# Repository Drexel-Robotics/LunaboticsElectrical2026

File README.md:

# Lunabotics Electrical 2025/2026 🚀⚡

Electrical and Embedded Systems repository for the Lunabotics 2025/2026 competition.

This repository contains firmware, hardware design files, and supporting documentation for the Lunabotics robot electrical subsystem — including embedded control (STM32 + Arduino), actuator drivers, power systems, and safety systems.

---

## 📌 Overview

The LunaboticsElectrical2026 project focuses on:

- Embedded motor & actuator control
- Custom PCB design (KiCAD)

This repo will grow throughout the season as firmware and hardware designs mature.

---

## 📂 Repository Structure

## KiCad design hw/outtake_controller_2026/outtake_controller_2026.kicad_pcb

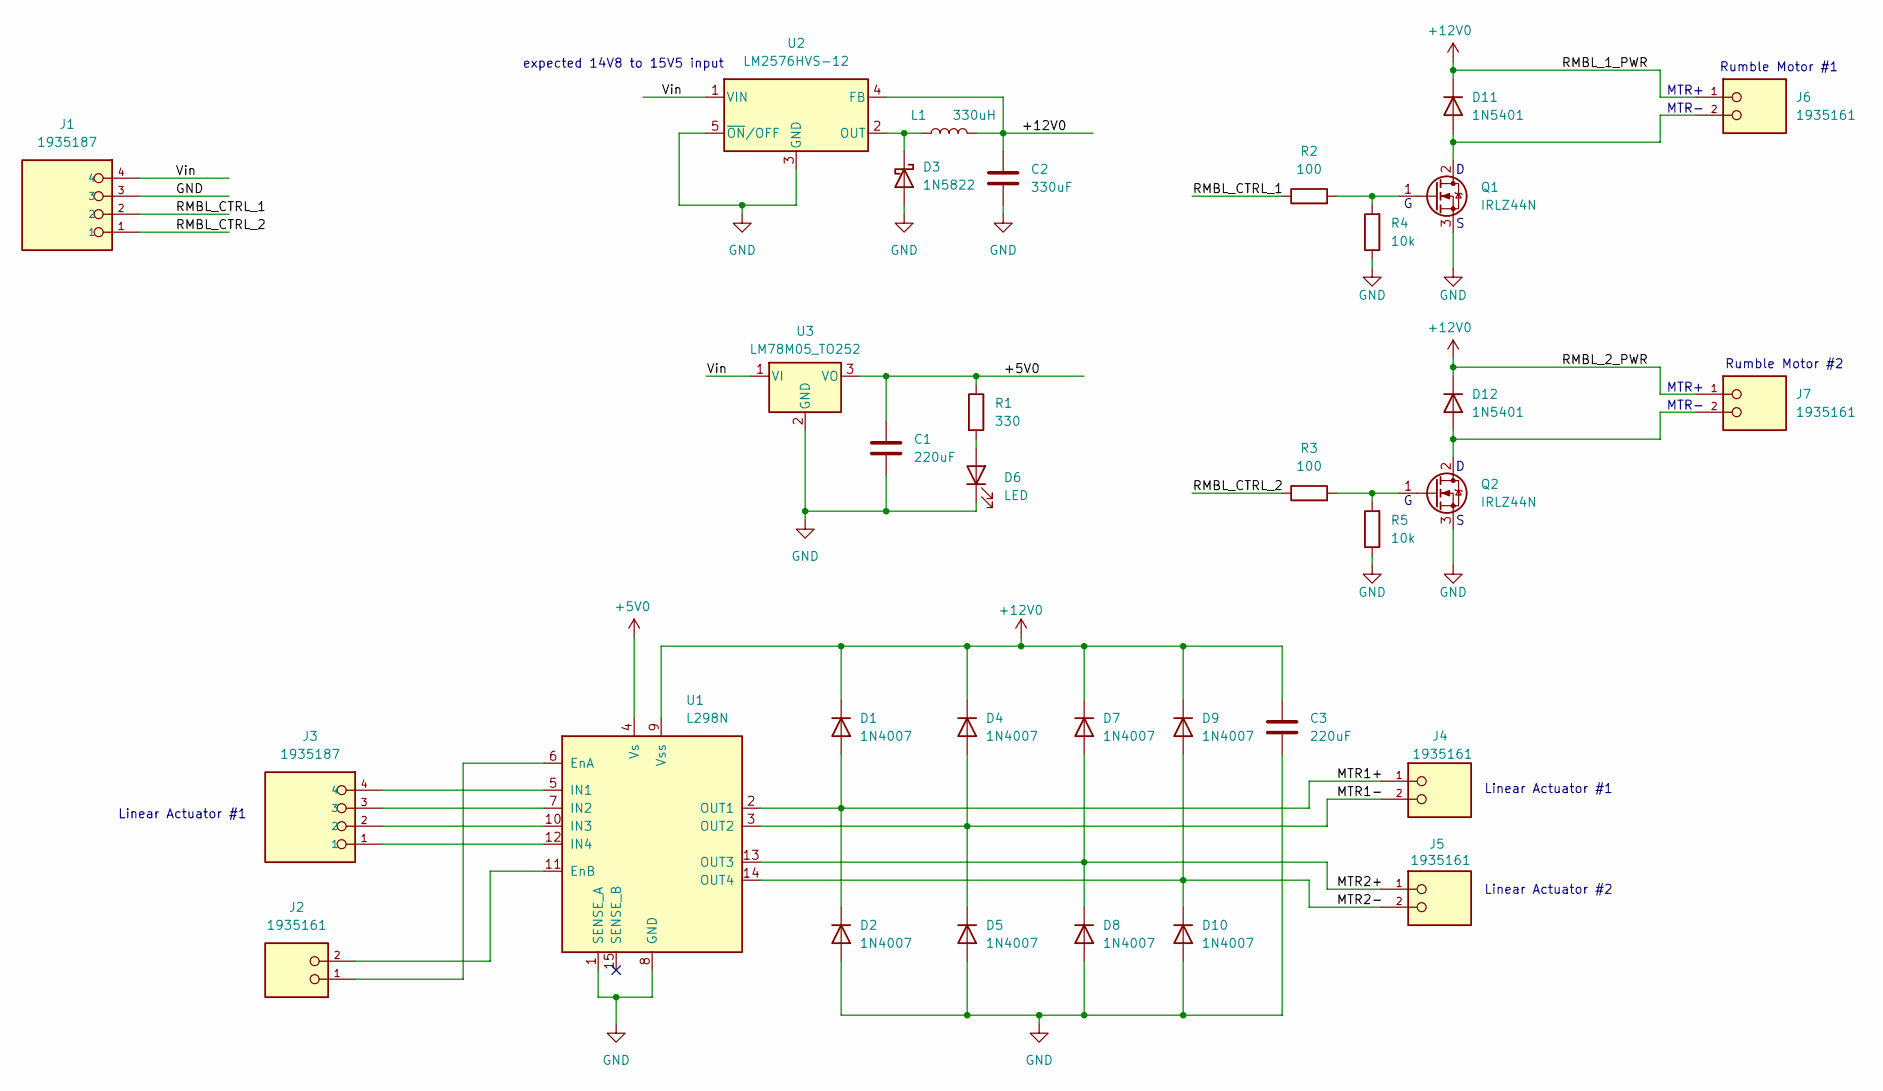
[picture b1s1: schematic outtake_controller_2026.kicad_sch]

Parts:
C1, C3: 220uF; C_Radial_D5.0mm_H11.0mm_P2.00mm
C2: 330uF; C_Radial_D5.0mm_H11.0mm_P2.00mm
D1, D2, D4, D5, D7, D8, D9, D10: 1N4007; D_DO-41_SOD81_P10.16mm_Horizontal
D3: 1N5822; D_DO-201AD_P15.24mm_Horizontal
D6: LED; LED_D5.0mm
D11, D12: 1N5401; D_DO-201AD_P15.24mm_Horizontal
J1, J3: 1935187; ScrewTerminal_4Block_1935187_PhoenixContact
J2, J4, J5, J6, J7: 1935161; ScrewTerminal_2Block_1935161_PhoenixContact
L1: 330uH; L_Axial_L9.5mm_D4.0mm_P12.70mm_Horizontal_Fastron_SMCC
Q1, Q2: IRLZ44N; TO-220-3_Vertical
R1: 330; R_Axial_DIN0207_L6.3mm_D2.5mm_P10.16mm_Horizontal
R2, R3: 100; R_Axial_DIN0207_L6.3mm_D2.5mm_P10.16mm_Horizontal
R4, R5: 10k; R_Axial_DIN0207_L6.3mm_D2.5mm_P10.16mm_Horizontal
U1: L298N; TO-220-15_P2.54x5.08mm_StaggerOdd_Lead4.58mm_Vertical
U2: LM2576HVS-12; TO-263-5_TabPin3
U3: LM78M05_TO252; TO-252-2

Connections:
+5V0: C1.1, R1.1, U1.4 (Vs), U3.3 (VO)
+12V0: C2.1, C3.1, D1.1 (K), D4.1 (K), D7.1 (K), D9.1 (K), D11.1 (K), D12.1 (K), J6.1, J7.1, L1.2, U1.9 (Vss), U2.4 (FB)
/MTR1+: D1.2 (A), D2.1 (K), J4.1, U1.2 (OUT1)
/MTR1-: D4.2 (A), D5.1 (K), J4.2, U1.3 (OUT2)
/MTR2+: D7.2 (A), D8.1 (K), J5.1, U1.13 (OUT3)
/MTR2-: D9.2 (A), D10.1 (K), J5.2, U1.14 (OUT4)
/RMBL_CTRL_1: J1.2, R2.1
/RMBL_CTRL_2: J1.1, R3.1
/Vin: J1.4, U2.1 (VIN), U3.1 (VI)
GND: C1.2, C2.2, C3.2, D2.2 (A), D3.2 (A), D5.2 (A), D6.1 (K), D8.2 (A), D10.2 (A), J1.3, Q1.3 (S), Q2.3 (S), R4.1, R5.1, U1.1 (SENSE_A), U1.8 (GND), U2.3 (GND), U2.5 (~ON/OFF), U3.2 (GND)
unnamed: D3.1 (K), L1.1, U2.2 (OUT)
unnamed: D6.2 (A), R1.2
unnamed: D11.2 (A), J6.2, Q1.2 (D)
unnamed: D12.2 (A), J7.2, Q2.2 (D)
unnamed: Q1.1 (G), R2.2, R4.2
unnamed: Q2.1 (G), R3.2, R5.2
unnamed: J2.1, U1.6 (EnA)
unnamed: J2.2, U1.11 (EnB)
unnamed: J3.4, U1.5 (IN1)
unnamed: J3.3, U1.7 (IN2)
unnamed: J3.2, U1.10 (IN3)
unnamed: J3.1, U1.12 (IN4)

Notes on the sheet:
Rumble Motor #2
MTR+
expected 14V8 to 15V5 input
Linear Actuator #1
MTR-
Linear Actuator #2
Rumble Motor #1

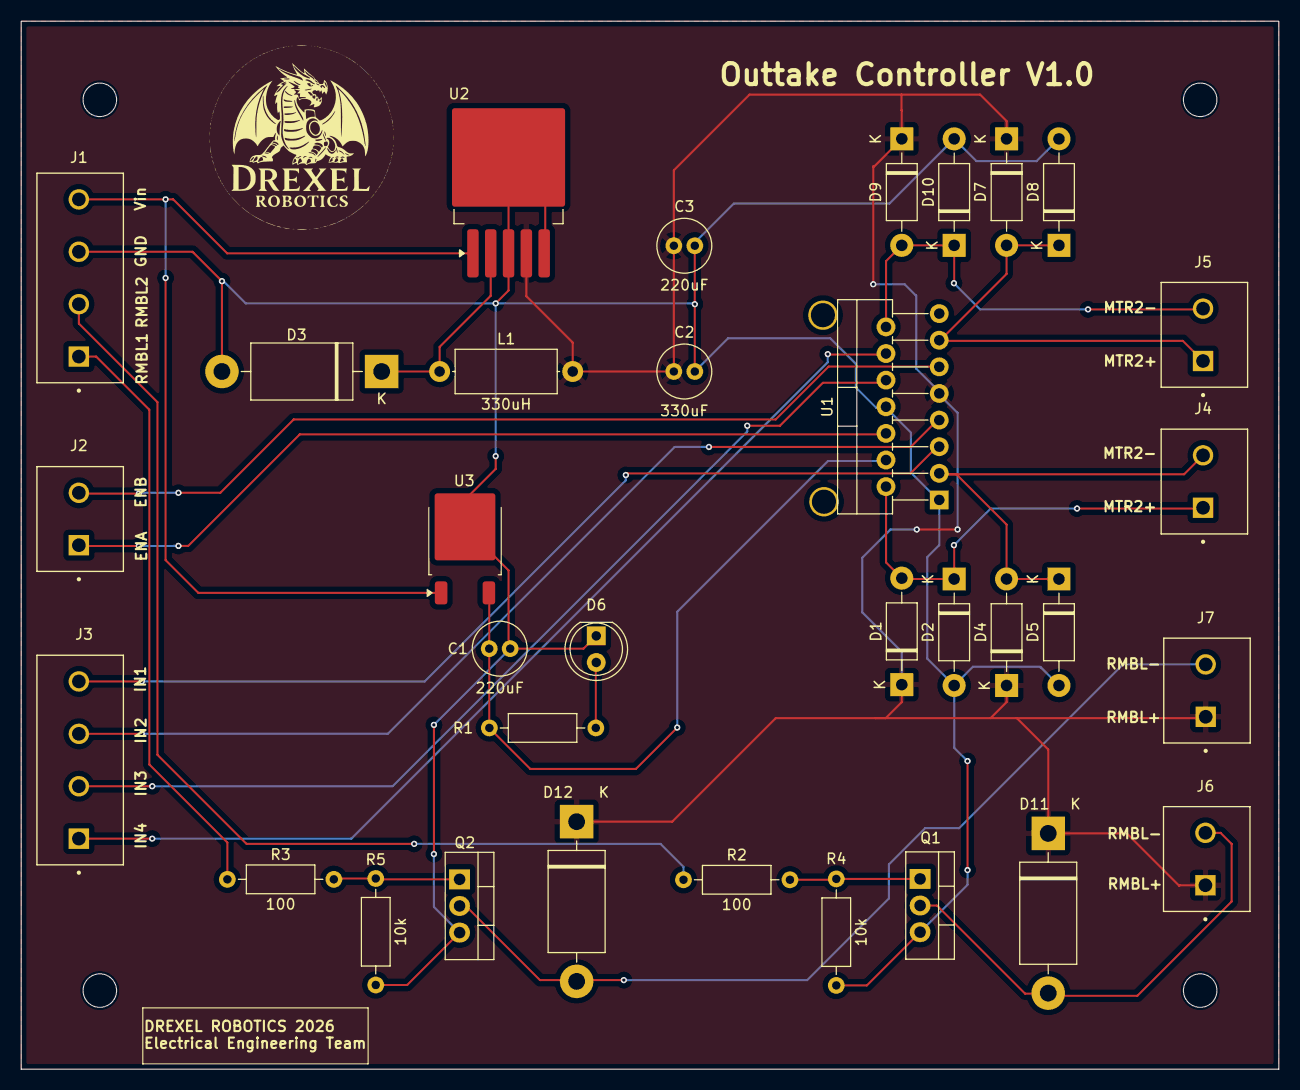
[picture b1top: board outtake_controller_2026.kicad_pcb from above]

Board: 2 copper layers, 120.0 x 100.0 mm, 33 parts (0 on the bottom side), 22 nets.

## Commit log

2026-02-14 first electrical commit! basic imu code example to read gyro data, arduino based.
2026-02-14 Create README.md for Lunabotics Electrical project
    Added initial README with project overview and structure.
2026-02-14 changed file structure for repository
2026-02-14 Actuator test code
2026-02-16 Created I2C wrapper for IMU read and writes
2026-02-21 Beginning of Actuator Controller
2026-03-07 file structure clean-up
2026-03-07 created symbol and footprints library, added known parts thus far, started top level schematic
2026-03-07 Finished actuator controller schematic
    Changes to add:
    Change the voltage regualtor
    Remove the arduino and add screw terminals
2026-03-31 Add Kalman Filter implementation for IMU data
2026-03-31 Add IMU interface for MPU9250 with FIR filtering
    This file implements an IMU (Inertial Measurement Unit) interface using the MPU9250 sensor. It includes functions for reading raw data, normalizing values, applying a FIR filter, and printing the res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
2026-03-31 updating schematics, pushing up for moho
2026-04-08 Add IMU interface for MPU9250 with FIR filtering, Arduino Implementation
    This file implements an IMU (Inertial Measurement Unit) interface using the MPU9250 sensor. It includes functions for reading raw data, normalizing values, applying a FIR filter, and printing the res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
2026-04-11 ManteakaMohoOuttakeEdits
2026-04-21 Add actuator control with Kalman filter implementation
2026-04-24 help me
    please
2026-05-05 finished actuator board, includes zip folder of project and gerbers used to order board
2026-05-05 reorganized file structure
2026-05-14 flipped inverse outtake extending and retracting functionality and added rumble functionality
2026-05-15 serial read fix
2026-05-15 serial read fix (#5)
